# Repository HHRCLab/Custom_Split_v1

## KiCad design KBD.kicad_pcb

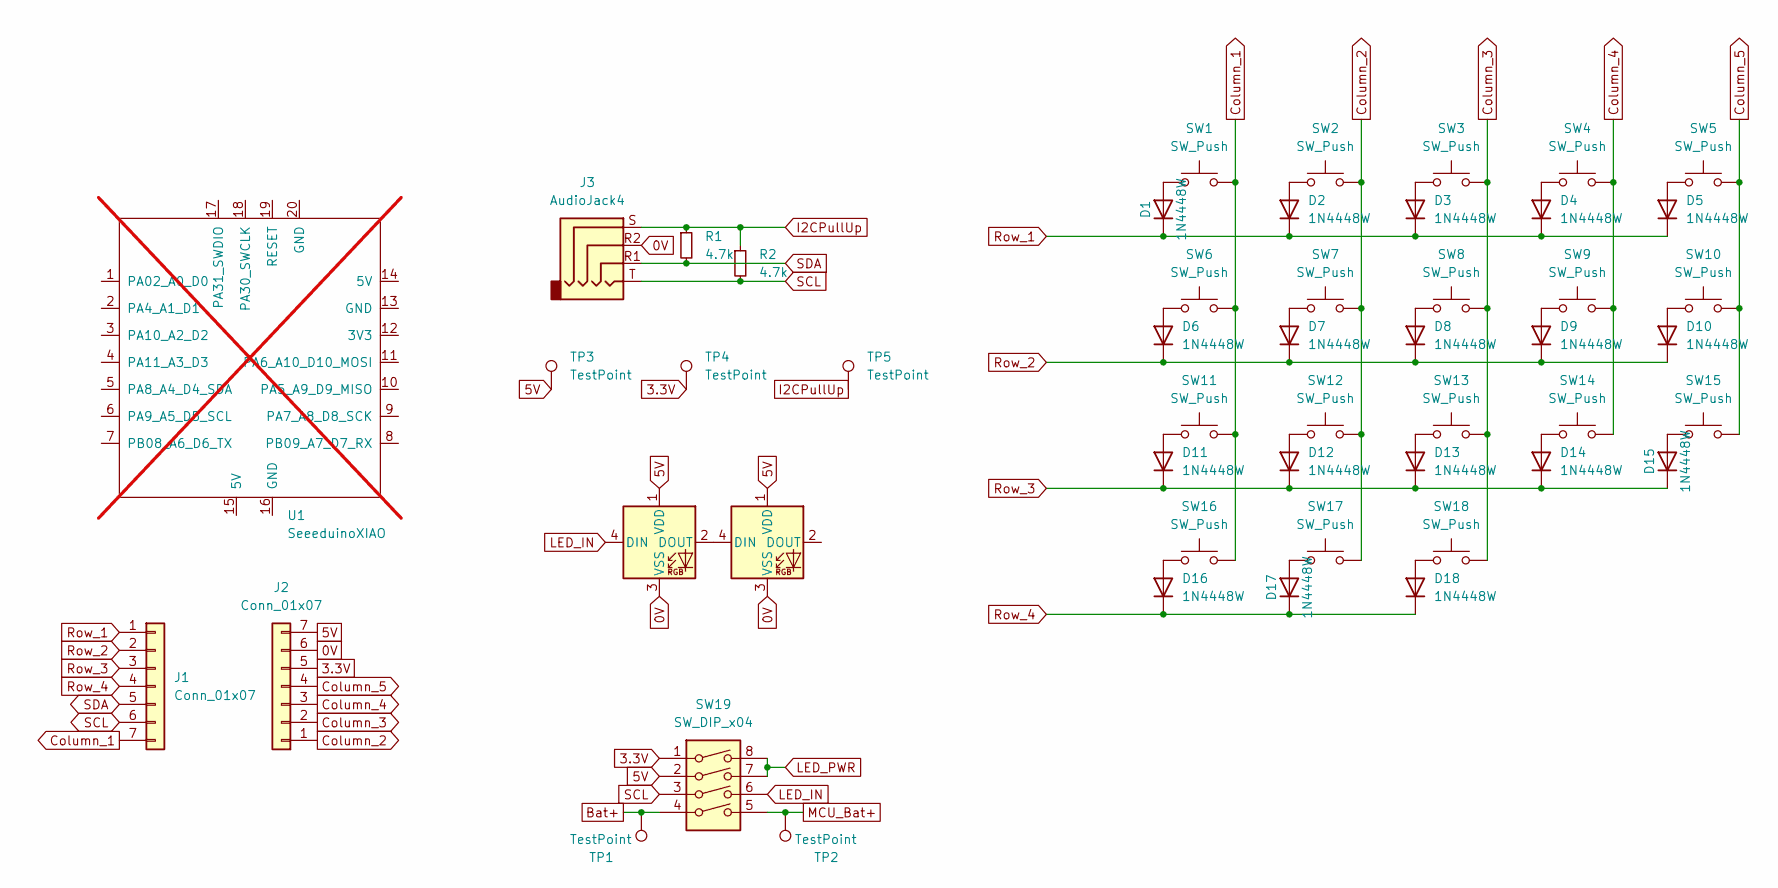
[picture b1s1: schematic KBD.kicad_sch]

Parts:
D1, D2, D3, D4, D5, D6, D7, D8, D9, D10, D11, D12, D13, D14, D15, D16, D17, D18: 1N4448W; D_SOD-123
D19, D20: WS2812B; LED_WS2812B_PLCC4_5.0x5.0mm_P3.2mm
J1, J2: Conn_01x07; Hirose_DF13-07P-1.25DS_1x07_P1.25mm_Horizontal
J3: AudioJack4; Jack_3.5mm_PJ320D_Horizontal
R1, R2: 4.7k; R_0805_2012Metric
SW1, SW2, SW3, SW4, SW5, SW6, SW7, SW8, SW9, SW10, SW11, SW12, SW13, SW14, SW15, SW16, SW17, SW18: SW_Push; Choc_reversible_17mmOutline
SW19: SW_DIP_x04; SW_DIP_SPSTx04_Slide_Copal_CHS-04A_W5.08mm_P1.27mm_JPin
TP1, TP2: TestPoint; TestPoint_THTPad_2.0x2.0mm_Drill1.0mm
TP3, TP4, TP5: TestPoint; TestPoint_Pad_1.0x1.0mm
U1: SeeeduinoXIAO; Seeeduino XIAO-MOUDLE14P-2.54-21X17.8MM; not fitted

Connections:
0V: D19.3 (VSS), D20.3 (VSS), J2.6, J3.R2; also elsewhere on the board
3.3V: J2.5, SW19.1, TP4.1; also elsewhere on the board
5V: D19.1 (VDD), D20.1 (VDD), J2.7, SW19.2, TP3.1; also elsewhere on the board
Bat+: SW19.4, TP1.1; also elsewhere on the board
Column_1: J1.7, SW1.2, SW6.2, SW11.2, SW16.2; also elsewhere on the board
Column_2: J2.1, SW2.2, SW7.2, SW12.2, SW17.2; also elsewhere on the board
Column_3: J2.2, SW3.2, SW8.2, SW13.2, SW18.2; also elsewhere on the board
Column_4: J2.3, SW4.2, SW9.2, SW14.2; also elsewhere on the board
Column_5: J2.4, SW5.2, SW10.2, SW15.2; also elsewhere on the board
I2CPullUp: J3.S, R1.1, R2.1, TP5.1; also elsewhere on the board
LED_IN: D19.4 (DIN), SW19.6; also elsewhere on the board
LED_PWR: SW19.7, SW19.8; also elsewhere on the board
MCU_Bat+: SW19.5, TP2.1; also elsewhere on the board
unnamed: D1.2 (A), SW1.1
unnamed: D2.2 (A), SW2.1
unnamed: D3.2 (A), SW3.1
unnamed: D4.2 (A), SW4.1
unnamed: D5.2 (A), SW5.1
unnamed: D6.2 (A), SW6.1
unnamed: D7.2 (A), SW7.1
unnamed: D8.2 (A), SW8.1
unnamed: D9.2 (A), SW9.1
unnamed: D10.2 (A), SW10.1
unnamed: D11.2 (A), SW11.1
unnamed: D12.2 (A), SW12.1
unnamed: D13.2 (A), SW13.1
unnamed: D14.2 (A), SW14.1
unnamed: D15.2 (A), SW15.1
unnamed: D16.2 (A), SW16.1
unnamed: D17.2 (A), SW17.1
unnamed: D18.2 (A), SW18.1
unnamed: D19.2 (DOUT), D20.4 (DIN)
Row_1: D1.1 (K), D2.1 (K), D3.1 (K), D4.1 (K), D5.1 (K), J1.1; also elsewhere on the board
Row_2: D6.1 (K), D7.1 (K), D8.1 (K), D9.1 (K), D10.1 (K), J1.2; also elsewhere on the board
Row_3: D11.1 (K), D12.1 (K), D13.1 (K), D14.1 (K), D15.1 (K), J1.3; also elsewhere on the board
Row_4: D16.1 (K), D17.1 (K), D18.1 (K), J1.4; also elsewhere on the board
SCL: J1.6, J3.T, R2.2, SW19.3; also elsewhere on the board
SDA: J1.5, J3.R1, R1.2; also elsewhere on the board

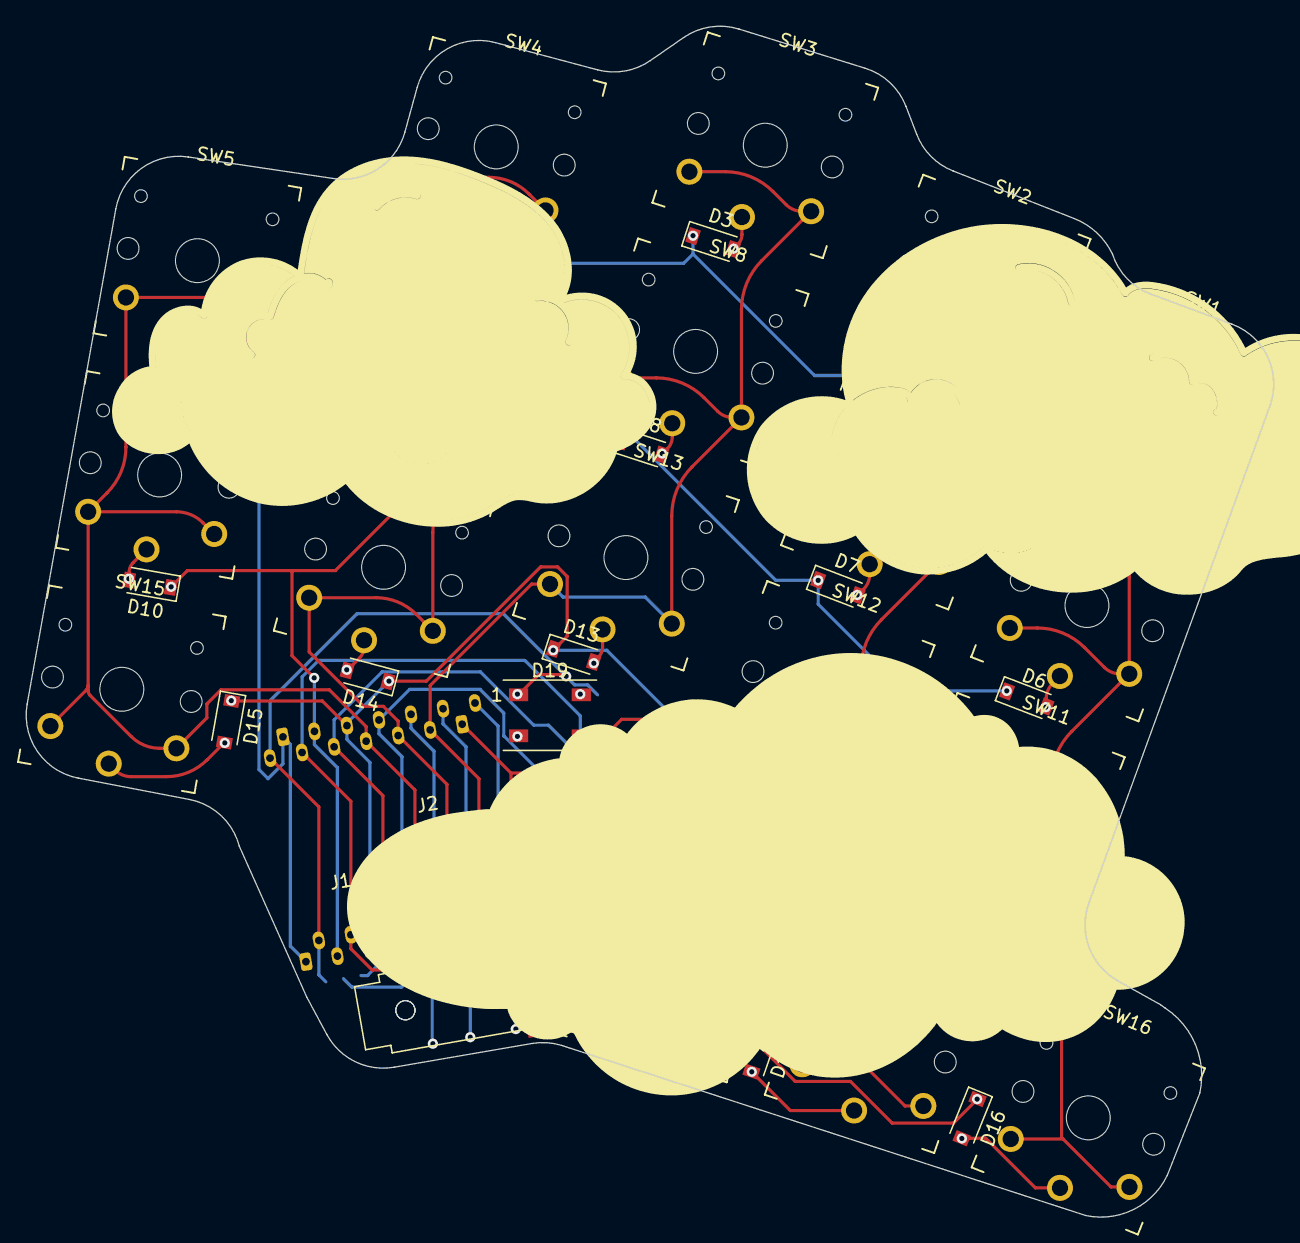
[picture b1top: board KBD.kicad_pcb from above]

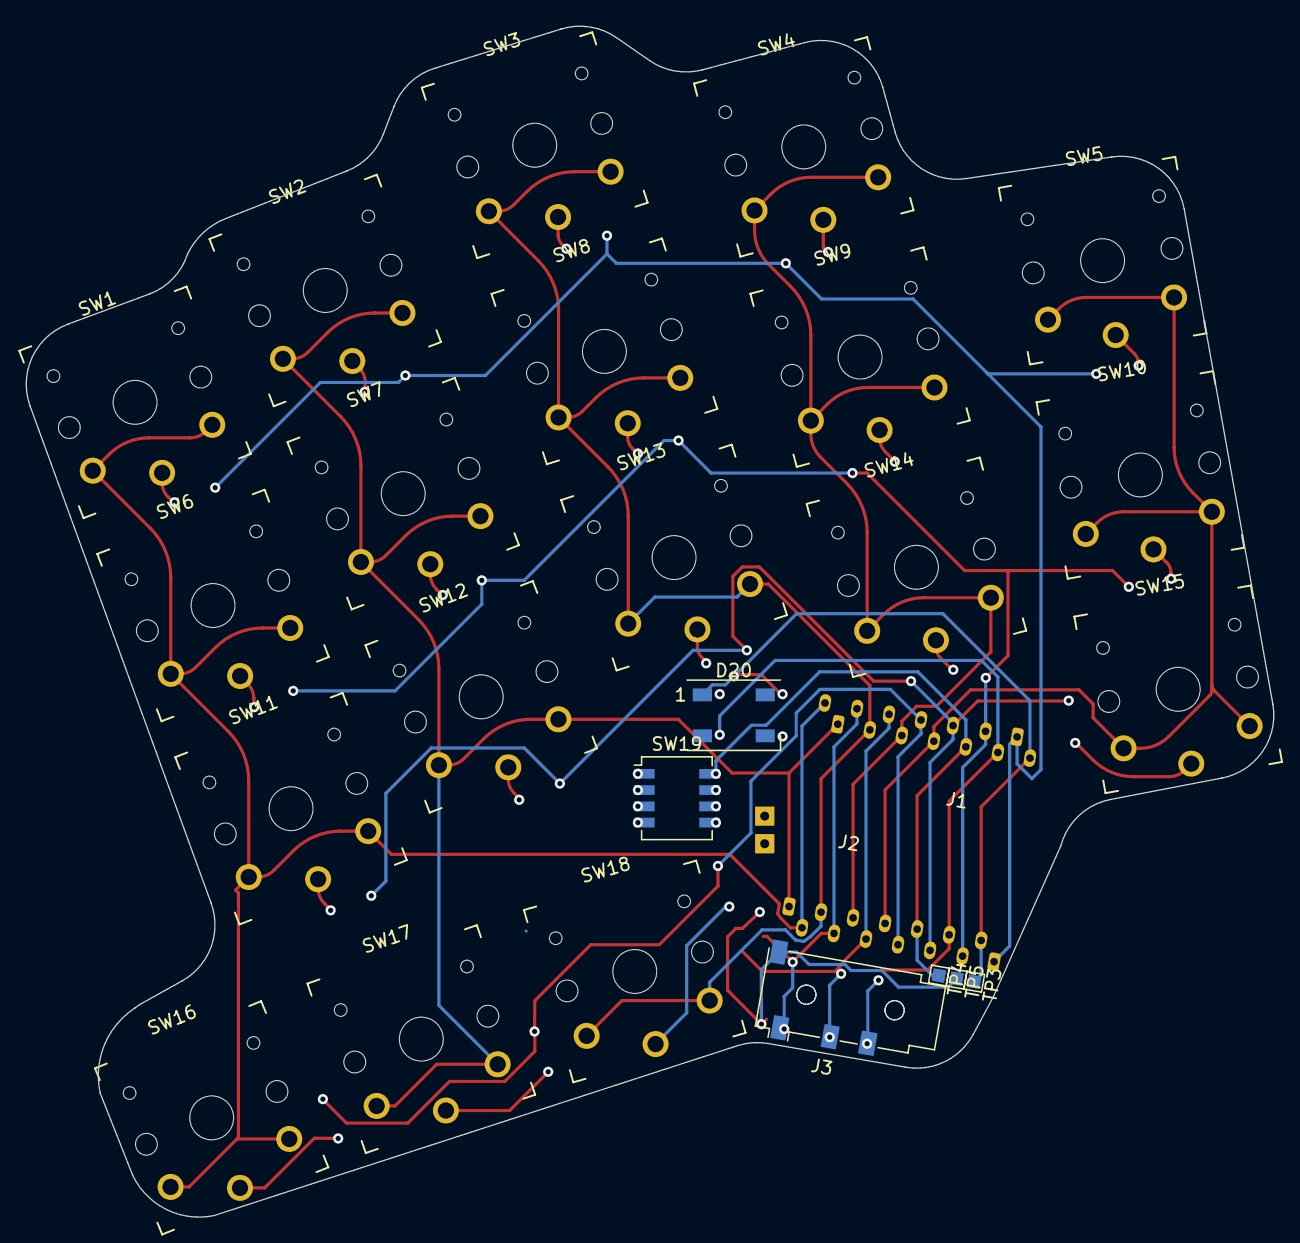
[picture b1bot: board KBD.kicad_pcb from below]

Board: 2 copper layers, 97.5 x 93.0 mm, 53 parts (8 on the bottom side), 38 nets.

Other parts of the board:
J1#2, J2#2: Conn_01x07; Hirose_DF13-07P-1.25DS_1x07_P1.25mm_Horizontal
J3#2: AudioJack4; Jack_3.5mm_PJ320D_Horizontal
SW19#2: SW_DIP_x04; SW_DIP_SPSTx04_Slide_Copal_CHS-04A_W5.08mm_P1.27mm_JPin

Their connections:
0V: J2#2.6, J3#2.R2; also elsewhere on the board
3.3V: J2#2.5, SW19#2.8; also elsewhere on the board
5V: J2#2.7, SW19#2.7; also elsewhere on the board
Bat+: SW19#2.5; also elsewhere on the board
Column_1: J1#2.7; also elsewhere on the board
Column_2: J2#2.1; also elsewhere on the board
Column_3: J2#2.2; also elsewhere on the board
Column_4: J2#2.3; also elsewhere on the board
Column_5: J2#2.4; also elsewhere on the board
I2CPullUp: J3#2.S; also elsewhere on the board
LED_IN: SW19#2.3; also elsewhere on the board
LED_PWR: SW19#2.1, SW19#2.2; also elsewhere on the board
MCU_Bat+: SW19#2.4; also elsewhere on the board
Row_1: J1#2.1; also elsewhere on the board
Row_2: J1#2.2; also elsewhere on the board
Row_3: J1#2.3; also elsewhere on the board
Row_4: J1#2.4; also elsewhere on the board
SCL: J1#2.6, J3#2.T, SW19#2.6; also elsewhere on the board
SDA: J1#2.5, J3#2.R1; also elsewhere on the board

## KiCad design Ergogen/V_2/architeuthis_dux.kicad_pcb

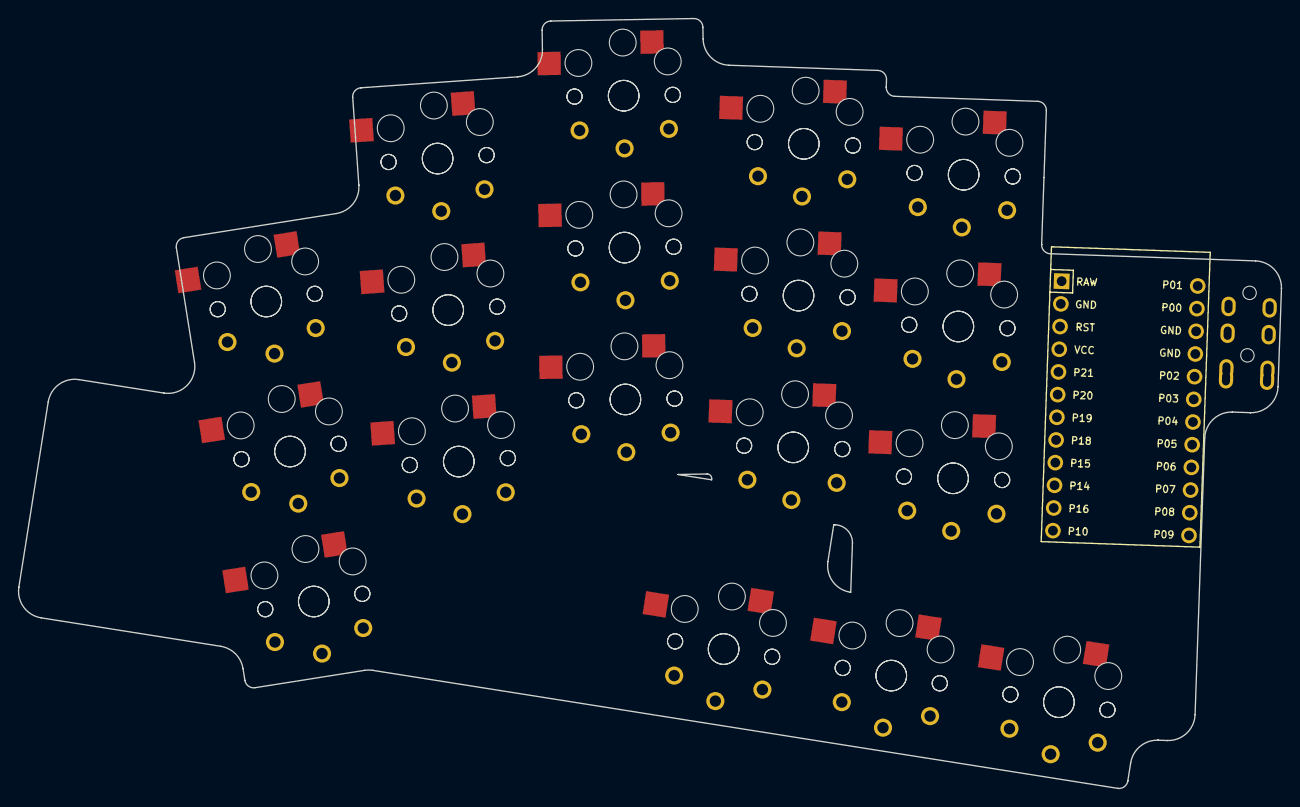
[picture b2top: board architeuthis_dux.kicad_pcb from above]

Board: 2 copper layers, 141.4 x 86.2 mm, 38 parts (0 on the bottom side), 4 nets, no tracks yet.

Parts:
MCU1: ProMicro
S1, S2, S3, S4, S5, S6, S7, S8, S9, S10, S11, S12, S13, S14, S15, S16, S17, S18, S19, S20, S21, S22, S23, S24, S25, S26, S27, S28, S29, S30, S31, S32, S33, S34, S35, S36: PG1350
TRRS1: TRRS-PJ-320A-dual

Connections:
=column_net: S1.1, S2.1, S3.1, S4.1, S5.1, S6.1, S7.1, S8.1, S9.1, S10.1, S11.1, S12.1, S13.1, S14.1, S15.1, S16.1, S17.1, S18.1, S19.1, S20.1, S21.1, S22.1, S23.1, S24.1, S25.1, S26.1, S27.1, S28.1, S29.1, S30.1, S31.1, S32.1, S33.1, S34.1, S35.1, S36.1
GND: MCU1.2, MCU1.15, MCU1.16, S1.2, S2.2, S3.2, S4.2, S5.2, S6.2, S7.2, S8.2, S9.2, S10.2, S11.2, S12.2, S13.2, S14.2, S15.2, S16.2, S17.2, S18.2, S19.2, S20.2, S21.2, S22.2, S23.2, S24.2, S25.2, S26.2, S27.2, S28.2, S29.2, S30.2, S31.2, S32.2, S33.2, S34.2, S35.2, S36.2, TRRS1.1, TRRS1.2
P2: MCU1.17, TRRS1.3
VCC: MCU1.4, TRRS1.4

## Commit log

2023-05-15 Before ergogen test
2023-05-25 Not much
2023-05-28 not much frHome
2023-06-03 worked on my pc with kicad 7.0
2023-06-04 aaaaaaa
2023-06-05 bbbbb
2023-06-06 bbbbbb1
2023-06-07 bbbbbb2
2023-06-13 TRRS version
2023-06-14 led not routed, else is done
2023-06-14 added svg's from home
2023-06-15 routing chaos
2023-06-16 Almost done
2023-06-17 Is this it?
